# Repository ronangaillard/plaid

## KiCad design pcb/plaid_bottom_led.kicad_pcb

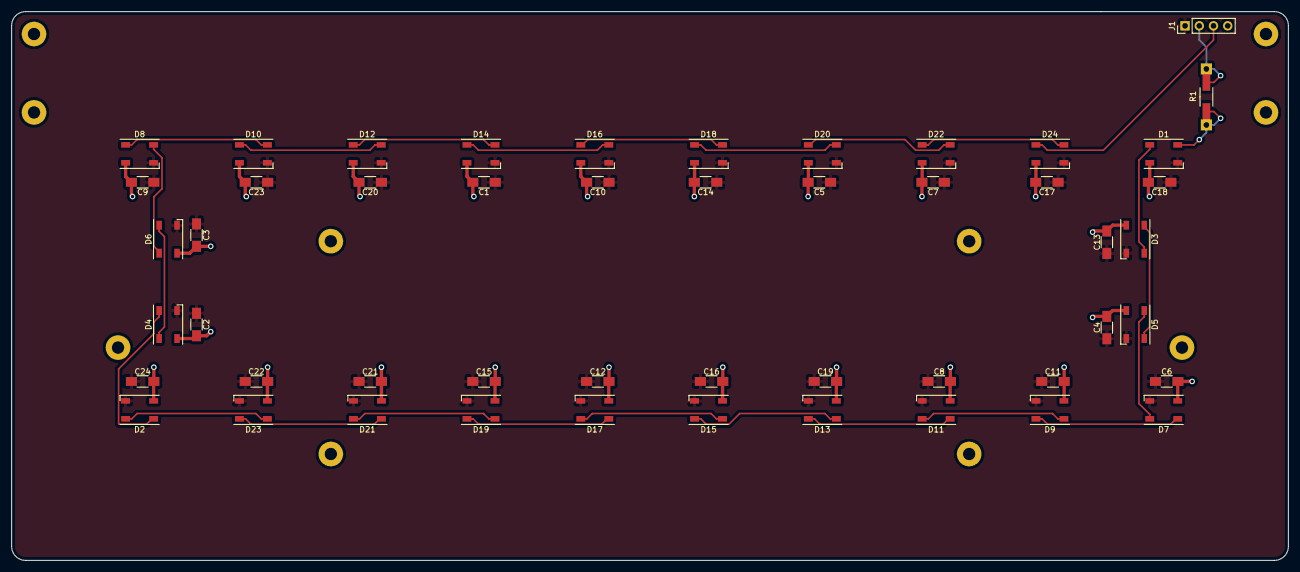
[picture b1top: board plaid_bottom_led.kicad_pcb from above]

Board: 2 copper layers, 228.0 x 98.0 mm, 60 parts (0 on the bottom side), 28 nets.

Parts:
C1, C2, C3, C4, C5, C6, C7, C8, C9, C10, C11, C12, C13, C14, C15, C16, C17, C18, C19, C20, C21, C22, C23, C24: 10uF; C_1206_HandSoldering
D1, D2, D3, D4, D5, D6, D7, D8, D9, D10, D11, D12, D13, D14, D15, D16, D17, D18, D19, D20, D21, D22, D23, D24: NeoPixel_THT; LED_WS2812B-PLCC4
H1, H2, H3, H4, H5, H6, H7, H8, H9, H10: M2; MountingHole_2.2mm_M2_Pad
J1: Conn_01x04_Male; Pin_Header_Straight_1x04_Pitch2.54mm
R1: 300; Resistor_SMD+THTuniversal_1206_RM10_HandSoldering

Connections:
+5V: C1.1, C2.1, C3.1, C4.1, C5.1, C6.1, C7.1, C8.1, C9.1, C10.1, C11.1, C12.1, C13.1, C14.1, C15.1, C16.1, C17.1, C18.1, C19.1, C20.1, C21.1, C22.1, C23.1, C24.1, D1.3, D2.3, D3.3, D4.3, D5.3, D6.3, D7.3, D8.3, D9.3, D10.3, D11.3, D12.3, D13.3, D14.3, D15.3, D16.3, D17.3, D18.3, D19.3, D20.3, D21.3, D22.3, D23.3, D24.3, J1.1
/DIN: D1.4, R1.1
/DOUT: D24.1, J1.3
GND: C1.2, C2.2, C3.2, C4.2, C5.2, C6.2, C7.2, C8.2, C9.2, C10.2, C11.2, C12.2, C13.2, C14.2, C15.2, C16.2, C17.2, C18.2, C19.2, C20.2, C21.2, C22.2, C23.2, C24.2, D1.2, D2.2, D3.2, D4.2, D5.2, D6.2, D7.2, D8.2, D9.2, D10.2, D11.2, D12.2, D13.2, D14.2, D15.2, D16.2, D17.2, D18.2, D19.2, D20.2, D21.2, D22.2, D23.2, D24.2, J1.4
unnamed: D1.1, D3.4
unnamed: D2.1, D4.4
unnamed: D2.4, D23.1
unnamed: D3.1, D5.4
unnamed: D4.1, D6.4
unnamed: D5.1, D7.4
unnamed: D6.1, D8.4
unnamed: D7.1, D9.4
unnamed: D10.1, D12.4
unnamed: D8.1, D10.4
unnamed: D11.1, D13.4
unnamed: D9.1, D11.4
unnamed: D12.1, D14.4
unnamed: D13.1, D15.4
unnamed: D14.1, D16.4
unnamed: D15.1, D17.4
unnamed: D16.1, D18.4
unnamed: D17.1, D19.4
unnamed: D18.1, D20.4
unnamed: D19.1, D21.4
unnamed: D20.1, D22.4
unnamed: D21.1, D23.4
unnamed: D22.1, D24.4
unnamed: J1.2, R1.2

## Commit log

2019-11-02 Add leds to bottom pcb
